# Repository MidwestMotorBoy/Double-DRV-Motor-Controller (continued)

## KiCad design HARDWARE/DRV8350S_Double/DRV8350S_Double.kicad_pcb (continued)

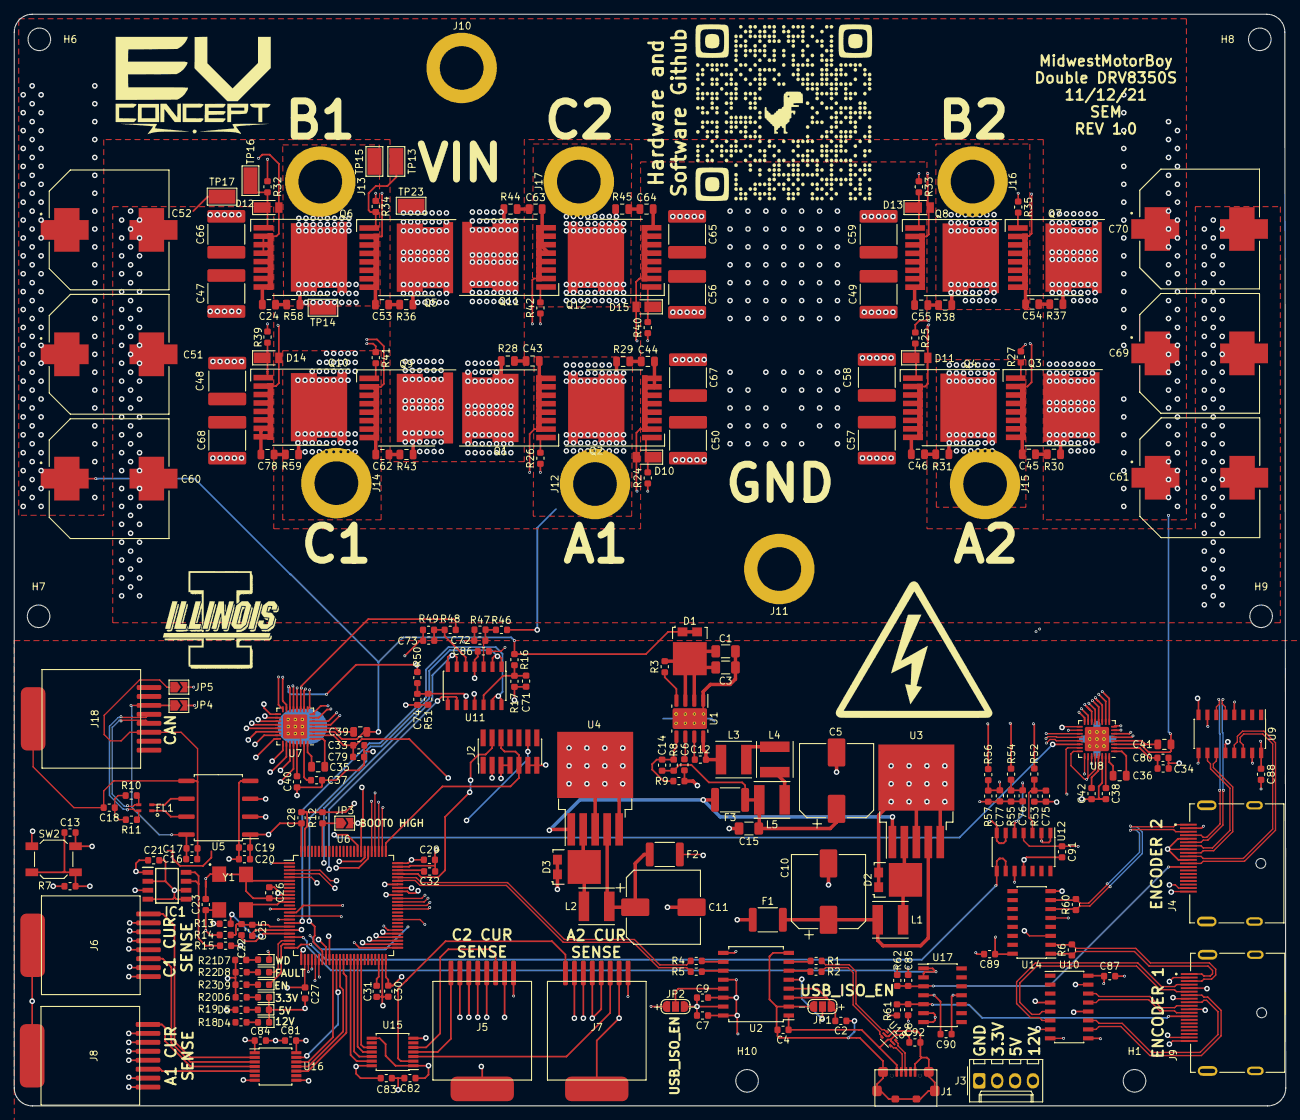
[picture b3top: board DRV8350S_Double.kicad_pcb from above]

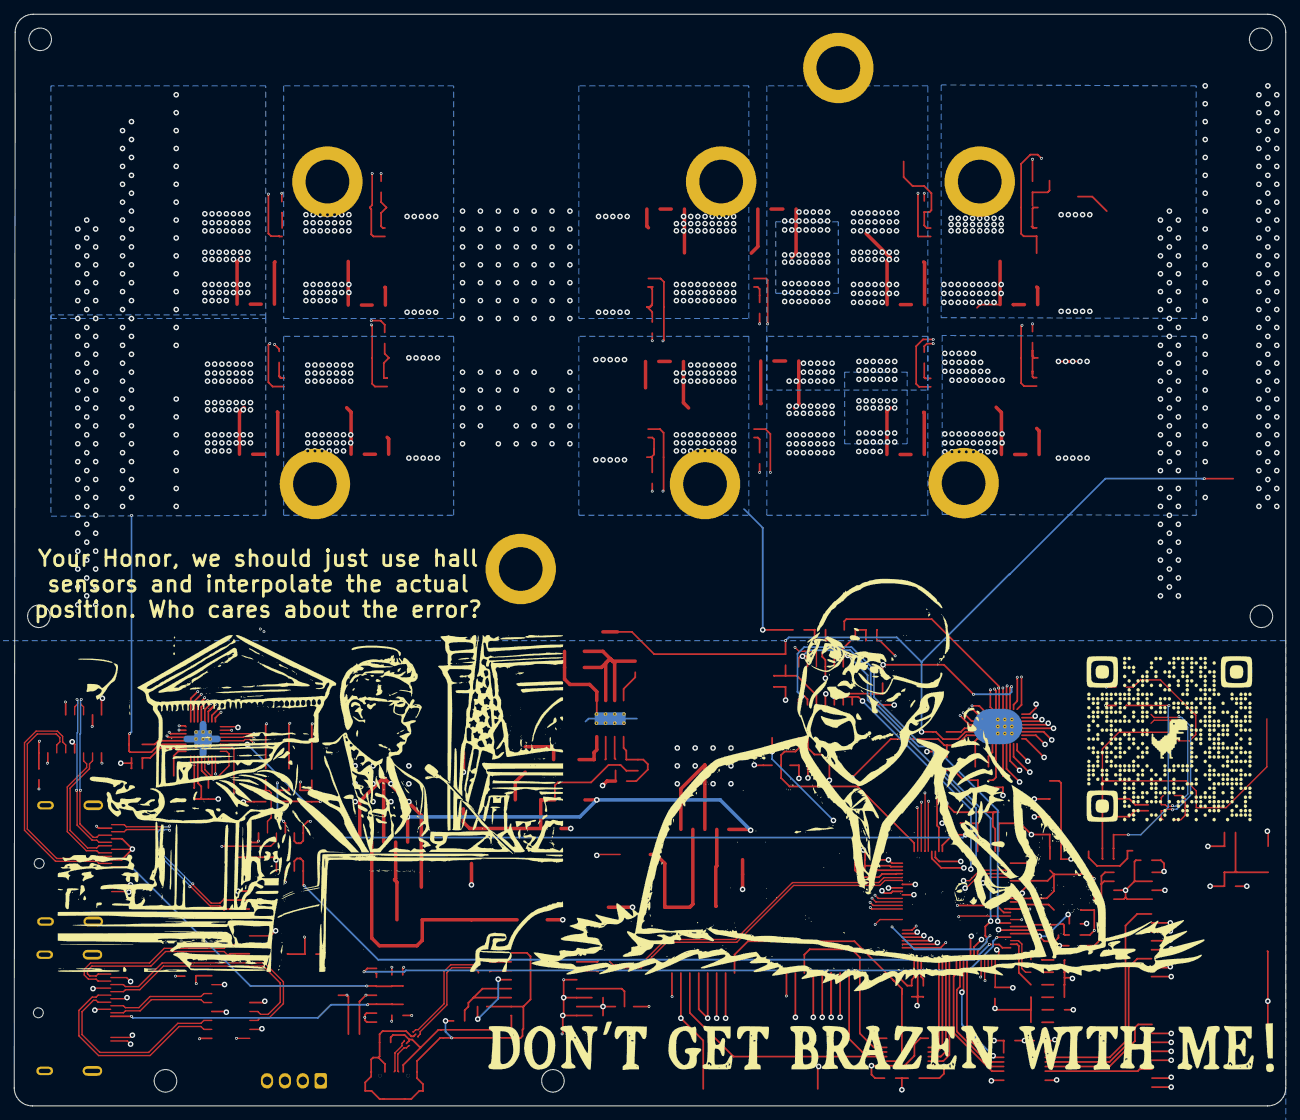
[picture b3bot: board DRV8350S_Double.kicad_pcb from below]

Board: 4 copper layers, 180.5 x 154.9 mm, 252 parts (3 on the bottom side), 192 nets.

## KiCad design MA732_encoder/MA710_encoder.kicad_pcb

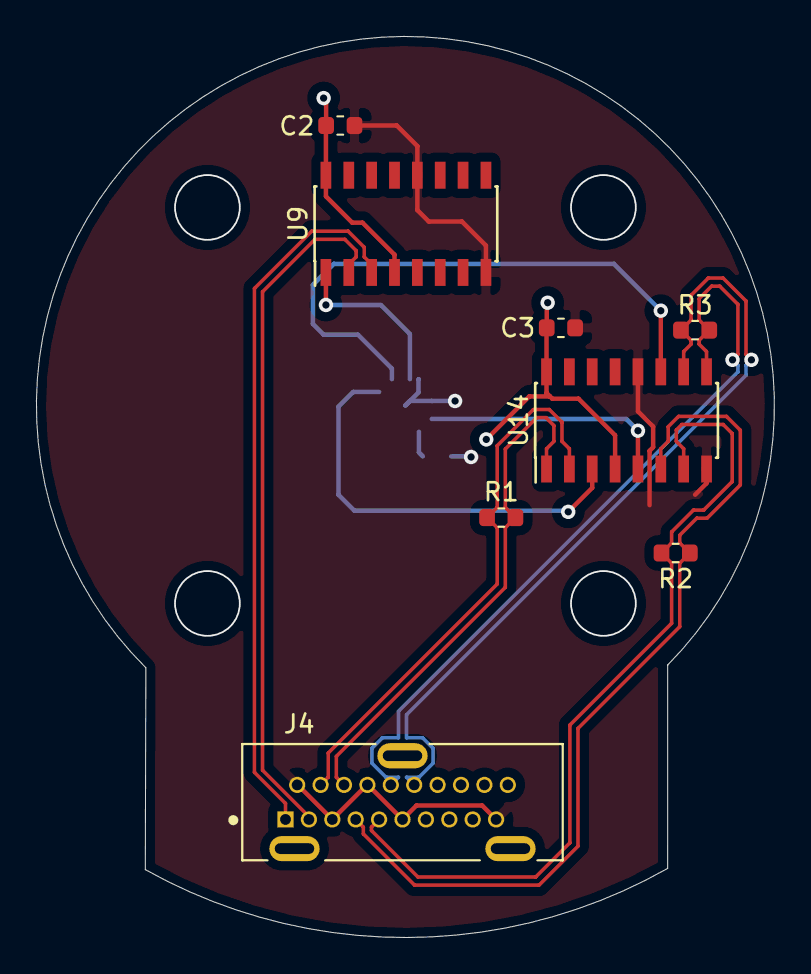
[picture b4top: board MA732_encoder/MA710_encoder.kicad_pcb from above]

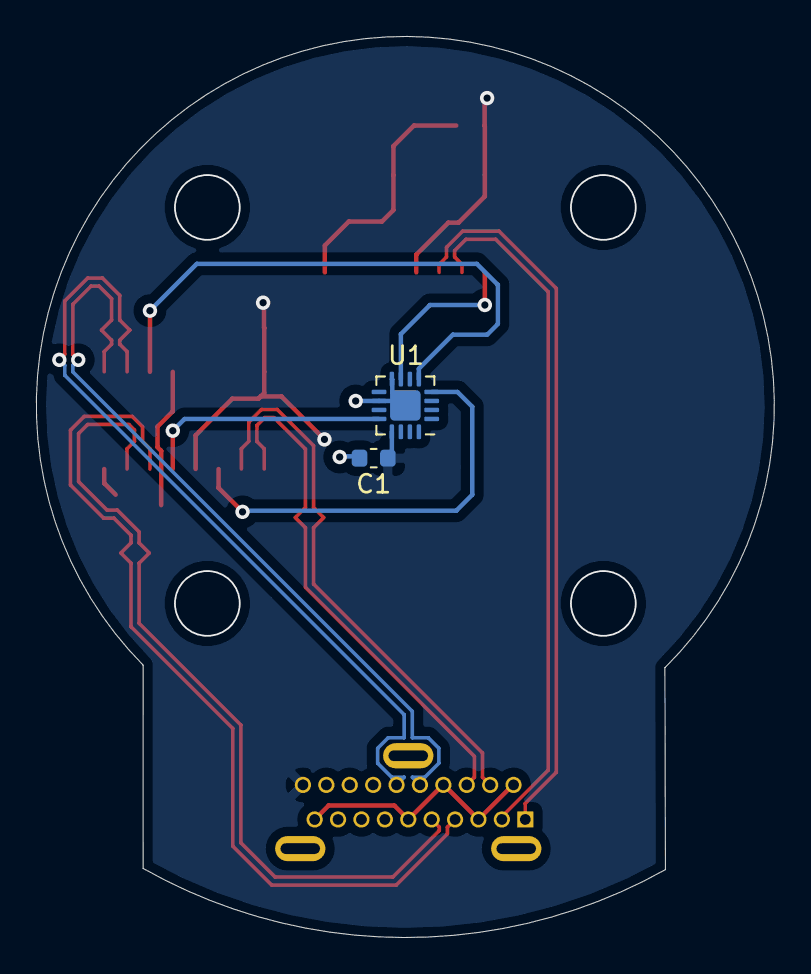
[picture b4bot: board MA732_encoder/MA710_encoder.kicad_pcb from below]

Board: 2 copper layers, 41.0 x 50.1 mm, 10 parts (2 on the bottom side), 14 nets.

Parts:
C1, C2, C3: 1uF; C_0603_1608Metric
J4: 47272-0001; TE_2041441-1
R1, R2, R3: 100Ω; R_0603_1608Metric
U1: MA730; QFN-16-1EP_3x3mm_P0.5mm_EP1.7x1.7mm
U9: SN65LVDS31D; SOIC-16_3.9x9.9mm_P1.27mm
U14: SN65LVDS33D; SOIC-16_3.9x9.9mm_P1.27mm

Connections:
+3V3: C1.1, C2.1, C3.1, J4.20, U1.13, U9.4, U9.16, U14.4, U14.16
GND: C1.2, C2.2, C3.2, J4.2, J4.5, J4.8, J4.11, J4.19, U1.8, U1.10, U1.17, U9.8, U9.12, U14.8, U14.12
SPI6_MISO: U1.7, U9.1
SPI6_MISO_+: J4.1, U9.3
SPI6_MISO_-: J4.3, U9.2
SPI6_MOSI: U1.4, U14.3
SPI6_MOSI_+: J4.4, R1.1, U14.2
SPI6_MOSI_-: J4.6, R1.2, U14.1
SPI6_SCK: U1.12, U14.5
SPI6_SCK_+: J4.7, R2.1, U14.6
SPI6_SCK_-: J4.9, R2.2, U14.7
SPI6_nSS: U1.5, U14.11
SPI6_nSS_+: J4.10, R3.1, U14.9
SPI6_nSS_-: J4.12, R3.2, U14.10

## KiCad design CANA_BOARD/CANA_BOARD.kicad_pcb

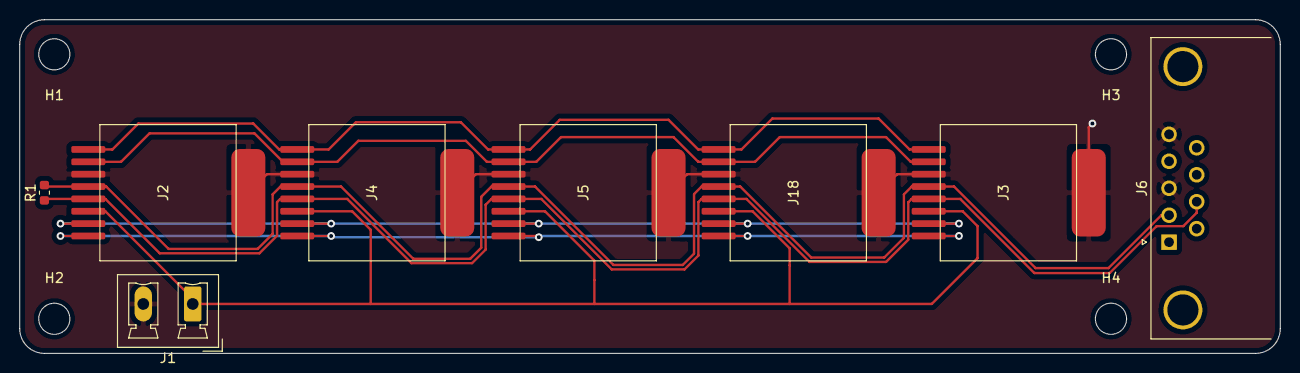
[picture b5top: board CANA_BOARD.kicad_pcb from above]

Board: 2 copper layers, 129.5 x 34.3 mm, 12 parts (0 on the bottom side), 8 nets.

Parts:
H1, H2, H3, H4: MountingHole; MountingHole_3.2mm_M3
J1: Conn_01x02_Male; PhoenixContact_MCV_1,5_2-G-5.08_1x02_P5.08mm_Vertical
J2, J3, J4, J5, J18: Conn_01x08; RCH-RC02015
J6: Conn_01x08; DSUB-9_Male_Horizontal_P2.77x2.84mm_EdgePinOffset7.70mm_Hou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
R1: 100Ω; R_0603_1608Metric

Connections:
5V_ISO: J1.1, J2.3, J3.3, J4.3, J5.3, J18.3
CAN_IN+: J2.4, J3.4, J4.4, J5.4, J6.7, J18.4, R1.1
CAN_IN-: J2.5, J3.5, J4.5, J5.5, J6.2, J18.5, R1.2
GND_ISO: J1.2, J2.6, J2.9, J3.6, J3.9, J4.6, J4.9, J5.6, J5.9, J6.3, J6.5, J18.6, J18.9
unnamed: J2.1, J3.1, J4.1, J5.1, J18.1
unnamed: J2.2, J3.2, J4.2, J5.2, J18.2
unnamed: J2.7, J3.7, J4.7, J5.7, J18.7
unnamed: J2.8, J3.8, J4.8, J5.8, J18.8

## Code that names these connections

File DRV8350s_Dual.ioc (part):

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Mcu.Name=STM32H730VBTx
Mcu.Package=LQFP100
Mcu.UserName=STM32H730VBTx
PA0.Mode=IN16-Single-Ended
PA0.Signal=ADC1_INP16
PA1.GPIOParameters=GPIO_Label
PA1.GPIO_Label=FAULT_LED
PA1.Signal=GPIO_Output
PA10.Signal=S_TIM1_CH3
PA11.Mode=Device_Only_FS
PA11.Signal=USB_OTG_HS_DM
PA12.Mode=Device_Only_FS
PA12.Signal=USB_OTG_HS_DP
PA13(JTMS/SWDIO).Mode=Serial_Wire
PA13(JTMS/SWDIO).Signal=DEBUG_JTMS-SWDIO
PA14(JTCK/SWCLK).Mode=Serial_Wire
PA14(JTCK/SWCLK).Signal=DEBUG_JTCK-SWCLK
PA15(JTDI).GPIOParameters=GPIO_PuPd
PA15(JTDI).GPIO_PuPd=GPIO_NOPULL
PA15(JTDI).Mode=NSS_Signal_Hard_Output
PA15(JTDI).Signal=SPI3_NSS
PA2.GPIOParameters=GPIO_Label
PA2.GPIO_Label=BRD_EN
PA2.Signal=GPIO_Output
PA3.Signal=ADCx_INP15
PA4.Mode=NSS_Signal_Hard_Output
PA4.Signal=SPI6_NSS
PA5.Mode=Full_Duplex_Master
PA5.Signal=SPI6_SCK
PA6.GPIOParameters=GPIO_PuPd
PA6.GPIO_PuPd=GPIO_NOPULL
PA6.Mode=Full_Duplex_Master
PA6.Signal=SPI6_MISO
PA7.Mode=Full_Duplex_Master
PA7.Signal=SPI6_MOSI
PA8.Signal=S_TIM1_CH1
PA9.Signal=S_TIM1_CH2
PB0.Signal=ADCx_INP9
PB1.Signal=S_DATAIN1DFSDM1
PB12.GPIOParameters=GPIO_PuPd
PB12.GPIO_PuPd=GPIO_NOPULL
PB12.Mode=NSS_Signal_Hard_Output
PB12.Signal=SPI2_NSS
PB13.Mode=Full_Duplex_Master
PB13.Signal=SPI2_SCK
PB14.GPIOParameters=GPIO_PuPd
PB14.GPIO_PuPd=GPIO_PULLUP
PB14.Mode=Full_Duplex_Master
PB14.Signal=SPI2_MISO
PB15.GPIOParameters=GPIO_PuPd
PB15.GPIO_PuPd=GPIO_NOPULL
PB15.Mode=Full_Duplex_Master
PB15.Signal=SPI2_MOSI
PB2.Signal=S_CKIN1DFSDM1
PC0.Signal=ADCx_INP10
PC1.Signal=ADCx_INP11
PC10.Mode=Full_Duplex_Master
PC10.Signal=SPI3_SCK
PC11.GPIOParameters=GPIO_PuPd
PC11.GPIO_PuPd=GPIO_PULLUP
PC11.Mode=Full_Duplex_Master
PC11.Signal=SPI3_MISO
PC12.Mode=Full_Duplex_Master
PC12.Signal=SPI3_MOSI
PC2_C.Mode=IN0-Single-Ended
PC2_C.Signal=ADC3_INP0
PC3_C.Mode=IN1-Single-Ended
PC3_C.Signal=ADC3_INP1
PC4.Signal=ADCx_INP4
PC5.Signal=ADCx_INP8
PC6.Signal=S_TIM8_CH1
PC7.Signal=S_TIM8_CH2
PC8.Signal=S_TIM8_CH3
PC9.GPIOParameters=GPIO_Label
PC9.GPIO_Label=INV1_EN
PC9.Signal=GPIO_Output
PD0.Mode=FDCAN_Activate
PD0.Signal=FDCAN1_RX
PD1.Mode=FDCAN_Activate
PD1.Signal=FDCAN1_TX
PD12.Signal=S_TIM4_CH1
PD15.GPIOParameters=GPIO_Label
PD15.GPIO_Label=INV2_EN
PD15.Signal=GPIO_Output
PD2.GPIOParameters=GPIO_Label
PD2.GPIO_Label=nFault2
PD2.Signal=GPIO_Input
PD3.GPIOParameters=GPIO_Label
PD3.GPIO_Label=DRV2_EN
PD3.Signal=GPIO_Output
PD8.GPIOParameters=GPIO_Label
PD8.GPIO_Label=FAULT1
PD8.Signal=GPIO_Input
PD9.GPIOParameters=GPIO_Label
PD9.GPIO_Label=DRV1_EN
PD9.Signal=GPIO_Output
PE10.Signal=S_DATAIN4DFSDM1
PE11.Signal=S_CKIN4DFSDM1
PE12.Signal=S_DATAIN5DFSDM1
PE13.Signal=S_CKIN5DFSDM1
PE2.Mode=Full_Duplex_Master
PE2.Signal=SPI4_SCK
PE4.GPIOParameters=GPIO_PuPd
PE4.GPIO_PuPd=GPIO_NOPULL
PE4.Mode=NSS_Signal_Hard_Output
PE4.Signal=SPI4_NSS
PE5.Mode=Full_Duplex_Master
PE5.Signal=SPI4_MISO
PE6.Mode=Full_Duplex_Master
PE6.Signal=SPI4_MOSI
PE7.Signal=S_DATAIN2DFSDM1
PE8.Signal=S_CKIN2DFSDM1
PH0-OSC_IN.Mode=HSE-External-Clock-Source
PH0-OSC_IN.Signal=RCC_OSC_IN
RCC.HSE_Timout=1000
RCC.HSE_VALUE=22118400
RCC.SYSCLKFreq_VALUE=549999900
RCC.SYSCLKSource=RCC_SYSCLKSOURCE_PLLCLK
board=custom

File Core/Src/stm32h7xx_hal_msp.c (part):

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    __HAL_RCC_GPIOC_CLK_ENABLE();
    __HAL_RCC_GPIOB_CLK_ENABLE();
    /**ADC1 GPIO Configuration
    PA0     ------> ADC1_INP16
    PC4     ------> ADC1_INP4
    PC5     ------> ADC1_INP8
    PB0     ------> ADC1_INP9
    */
    GPIO_InitStruct.Pin = GPIO_PIN_0;
    GPIO_InitStruct.Mode = GPIO_MODE_ANALOG;
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    __HAL_RCC_GPIOC_CLK_ENABLE();
    __HAL_RCC_GPIOA_CLK_ENABLE();
    /**ADC2 GPIO Configuration
    PC0     ------> ADC2_INP10
    PC1     ------> ADC2_INP11
    PA3     ------> ADC2_INP15
    */
    GPIO_InitStruct.Pin = GPIO_PIN_0|GPIO_PIN_1;
    GPIO_InitStruct.Mode = GPIO_MODE_ANALOG;
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    }

    /**ADC1 GPIO Configuration
    PA0     ------> ADC1_INP16
    PC4     ------> ADC1_INP4
    PC5     ------> ADC1_INP8
    PB0     ------> ADC1_INP9
    */
    HAL_GPIO_DeInit(GPIOA, GPIO_PIN_0);

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    }

    /**ADC2 GPIO Configuration
    PC0     ------> ADC2_INP10
    PC1     ------> ADC2_INP11
    PA3     ------> ADC2_INP15
    */
    HAL_GPIO_DeInit(GPIOC, GPIO_PIN_0|GPIO_PIN_1);

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    __HAL_RCC_GPIOB_CLK_ENABLE();
    __HAL_RCC_GPIOE_CLK_ENABLE();
    /**DFSDM1 GPIO Configuration
    PB1     ------> DFSDM1_DATIN1
    PB2     ------> DFSDM1_CKIN1
    PE7     ------> DFSDM1_DATIN2
    PE8     ------> DFSDM1_CKIN2
    PE10     ------> DFSDM1_DATIN4
    PE11     ------> DFSDM1_CKIN4
    PE12     ------> DFSDM1_DATIN5
    PE13     ------> DFSDM1_CKIN5
    */
    GPIO_InitStruct.Pin = GPIO_PIN_1;
    GPIO_InitStruct.Mode = GPIO_MODE_AF_PP;
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    __HAL_RCC_GPIOB_CLK_ENABLE();
    __HAL_RCC_GPIOE_CLK_ENABLE();
    /**DFSDM1 GPIO Configuration
    PB1     ------> DFSDM1_DATIN1
    PB2     ------> DFSDM1_CKIN1
    PE7     ------> DFSDM1_DATIN2
    PE8     ------> DFSDM1_CKIN2
    PE10     ------> DFSDM1_DATIN4
    PE11     ------> DFSDM1_CKIN4
    PE12     ------> DFSDM1_DATIN5
    PE13     ------> DFSDM1_CKIN5
    */
    GPIO_InitStruct.Pin = GPIO_PIN_1;
    GPIO_InitStruct.Mode = GPIO_MODE_AF_PP;
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    __HAL_RCC_DFSDM1_CLK_DISABLE();

    /**DFSDM1 GPIO Configuration
    PB1     ------> DFSDM1_DATIN1
    PB2     ------> DFSDM1_CKIN1
    PE7     ------> DFSDM1_DATIN2
    PE8     ------> DFSDM1_CKIN2
    PE10     ------> DFSDM1_DATIN4
    PE11     ------> DFSDM1_CKIN4
    PE12     ------> DFSDM1_DATIN5
    PE13     ------> DFSDM1_CKIN5
    */
    HAL_GPIO_DeInit(GPIOB, GPIO_PIN_1|GPIO_PIN_2);

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    __HAL_RCC_DFSDM1_CLK_DISABLE();

    /**DFSDM1 GPIO Configuration
    PB1     ------> DFSDM1_DATIN1
    PB2     ------> DFSDM1_CKIN1
    PE7     ------> DFSDM1_DATIN2
    PE8     ------> DFSDM1_CKIN2
    PE10     ------> DFSDM1_DATIN4
    PE11     ------> DFSDM1_CKIN4
    PE12     ------> DFSDM1_DATIN5
    PE13     ------> DFSDM1_CKIN5
    */
    HAL_GPIO_DeInit(GPIOB, GPIO_PIN_1|GPIO_PIN_2);

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
    __HAL_RCC_GPIOD_CLK_ENABLE();
    /**FDCAN1 GPIO Configuration
    PD0     ------> FDCAN1_RX
    PD1     ------> FDCAN1_TX
    */
    GPIO_InitStruct.Pin = GPIO_PIN_0|GPIO_PIN_1;
    GPIO_InitStruct.Mode = GPIO_MODE_AF_PP;
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    __HAL_RCC_FDCAN_CLK_DISABLE();

    /**FDCAN1 GPIO Configuration
    PD0     ------> FDCAN1_RX
    PD1     ------> FDCAN1_TX
    */
    HAL_GPIO_DeInit(GPIOD, GPIO_PIN_0|GPIO_PIN_1);

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
    __HAL_RCC_GPIOB_CLK_ENABLE();
    /**SPI2 GPIO Configuration
    PB12     ------> SPI2_NSS
    PB13     ------> SPI2_SCK
    PB14     ------> SPI2_MISO
    PB15     ------> SPI2_MOSI
    */
    GPIO_InitStruct.Pin = GPIO_PIN_12|GPIO_PIN_13|GPIO_PIN_15;
    GPIO_InitStruct.Mode = GPIO_MODE_AF_PP;
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    __HAL_RCC_GPIOA_CLK_ENABLE();
    __HAL_RCC_GPIOC_CLK_ENABLE();
    /**SPI3 GPIO Configuration
    PA15(JTDI)     ------> SPI3_NSS
    PC10     ------> SPI3_SCK
    PC11     ------> SPI3_MISO
    PC12     ------> SPI3_MOSI
    */
    GPIO_InitStruct.Pin = GPIO_PIN_15;
    GPIO_InitStruct.Mode = GPIO_MODE_AF_PP;
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
    __HAL_RCC_GPIOE_CLK_ENABLE();
    /**SPI4 GPIO Configuration
    PE2     ------> SPI4_SCK
    PE4     ------> SPI4_NSS
    PE5     ------> SPI4_MISO
    PE6     ------> SPI4_MOSI
    */
    GPIO_InitStruct.Pin = GPIO_PIN_2|GPIO_PIN_4|GPIO_PIN_5|GPIO_PIN_6;
    GPIO_InitStruct.Mode = GPIO_MODE_AF_PP;
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
    __HAL_RCC_GPIOA_CLK_ENABLE();
    /**SPI6 GPIO Configuration
    PA4     ------> SPI6_NSS
    PA5     ------> SPI6_SCK
    PA6     ------> SPI6_MISO
    PA7     ------> SPI6_MOSI
    */
    GPIO_InitStruct.Pin = GPIO_PIN_4|GPIO_PIN_5|GPIO_PIN_6|GPIO_PIN_7;
    GPIO_InitStruct.Mode = GPIO_MODE_AF_PP;
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    __HAL_RCC_SPI2_CLK_DISABLE();

    /**SPI2 GPIO Configuration
    PB12     ------> SPI2_NSS
    PB13     ------> SPI2_SCK
    PB14     ------> SPI2_MISO
    PB15     ------> SPI2_MOSI
    */
    HAL_GPIO_DeInit(GPIOB, GPIO_PIN_12|GPIO_PIN_13|GPIO_PIN_14|GPIO_PIN_15);

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    __HAL_RCC_SPI3_CLK_DISABLE();

    /**SPI3 GPIO Configuration
    PA15(JTDI)     ------> SPI3_NSS
    PC10     ------> SPI3_SCK
    PC11     ------> SPI3_MISO
    PC12     ------> SPI3_MOSI
    */
    HAL_GPIO_DeInit(GPIOA, GPIO_PIN_15);

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    __HAL_RCC_SPI4_CLK_DISABLE();

    /**SPI4 GPIO Configuration
    PE2     ------> SPI4_SCK
    PE4     ------> SPI4_NSS
    PE5     ------> SPI4_MISO
    PE6     ------> SPI4_MOSI
    */
    HAL_GPIO_DeInit(GPIOE, GPIO_PIN_2|GPIO_PIN_4|GPIO_PIN_5|GPIO_PIN_6);

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    __HAL_RCC_SPI6_CLK_DISABLE();

    /**SPI6 GPIO Configuration
    PA4     ------> SPI6_NSS
    PA5     ------> SPI6_SCK
    PA6     ------> SPI6_MISO
    PA7     ------> SPI6_MOSI
    */
    HAL_GPIO_DeInit(GPIOA, GPIO_PIN_4|GPIO_PIN_5|GPIO_PIN_6|GPIO_PIN_7);

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  /* USER CODE END TIM1_MspPostInit 0 */
    __HAL_RCC_GPIOA_CLK_ENABLE();
    /**TIM1 GPIO Configuration
    PA8     ------> TIM1_CH1
    PA9     ------> TIM1_CH2
    PA10     ------> TIM1_CH3
    */
    GPIO_InitStruct.Pin = GPIO_PIN_8|GPIO_PIN_9|GPIO_PIN_10;
    GPIO_InitStruct.Mode = GPIO_MODE_AF_PP;
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
    __HAL_RCC_GPIOD_CLK_ENABLE();
    /**TIM4 GPIO Configuration
    PD12     ------> TIM4_CH1
    */
    GPIO_InitStruct.Pin = GPIO_PIN_12;
    GPIO_InitStruct.Mode = GPIO_MODE_AF_PP;
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
    __HAL_RCC_GPIOC_CLK_ENABLE();
    /**TIM8 GPIO Configuration
    PC6     ------> TIM8_CH1
    PC7     ------> TIM8_CH2
    PC8     ------> TIM8_CH3
    */
    GPIO_InitStruct.Pin = GPIO_PIN_6|GPIO_PIN_7|GPIO_PIN_8;
    GPIO_InitStruct.Mode = GPIO_MODE_AF_PP;
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
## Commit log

2021-11-29 Init commit
2021-11-29 fixed iso_gnd miss
2022-02-12 Backing up current design
    Fucked up something with STM32 and displayport is dumb
2022-06-18 Commiting a ton of work, working current, position sensors, motion pos calibration routine done
2022-06-18 Moved hardware files into the hardware folder
2022-06-18 cleanup
2022-06-25 Renaming
2022-06-25 Silk Screen Changes
